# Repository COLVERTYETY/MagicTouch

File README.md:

# Magic touch

This is project implementation of Disney's Touché.

references:

[Dzl's project](http://dzlsevilgeniuslair.blogspot.com/2012/05/arduino-do-touche-dance.html)

[instructables by mashobye](https://www.instructables.com/Touche-for-Arduino-Advanced-touch-sensing/)

[github by illutron](https://github.com/Illutron/AdvancedTouchSensing)

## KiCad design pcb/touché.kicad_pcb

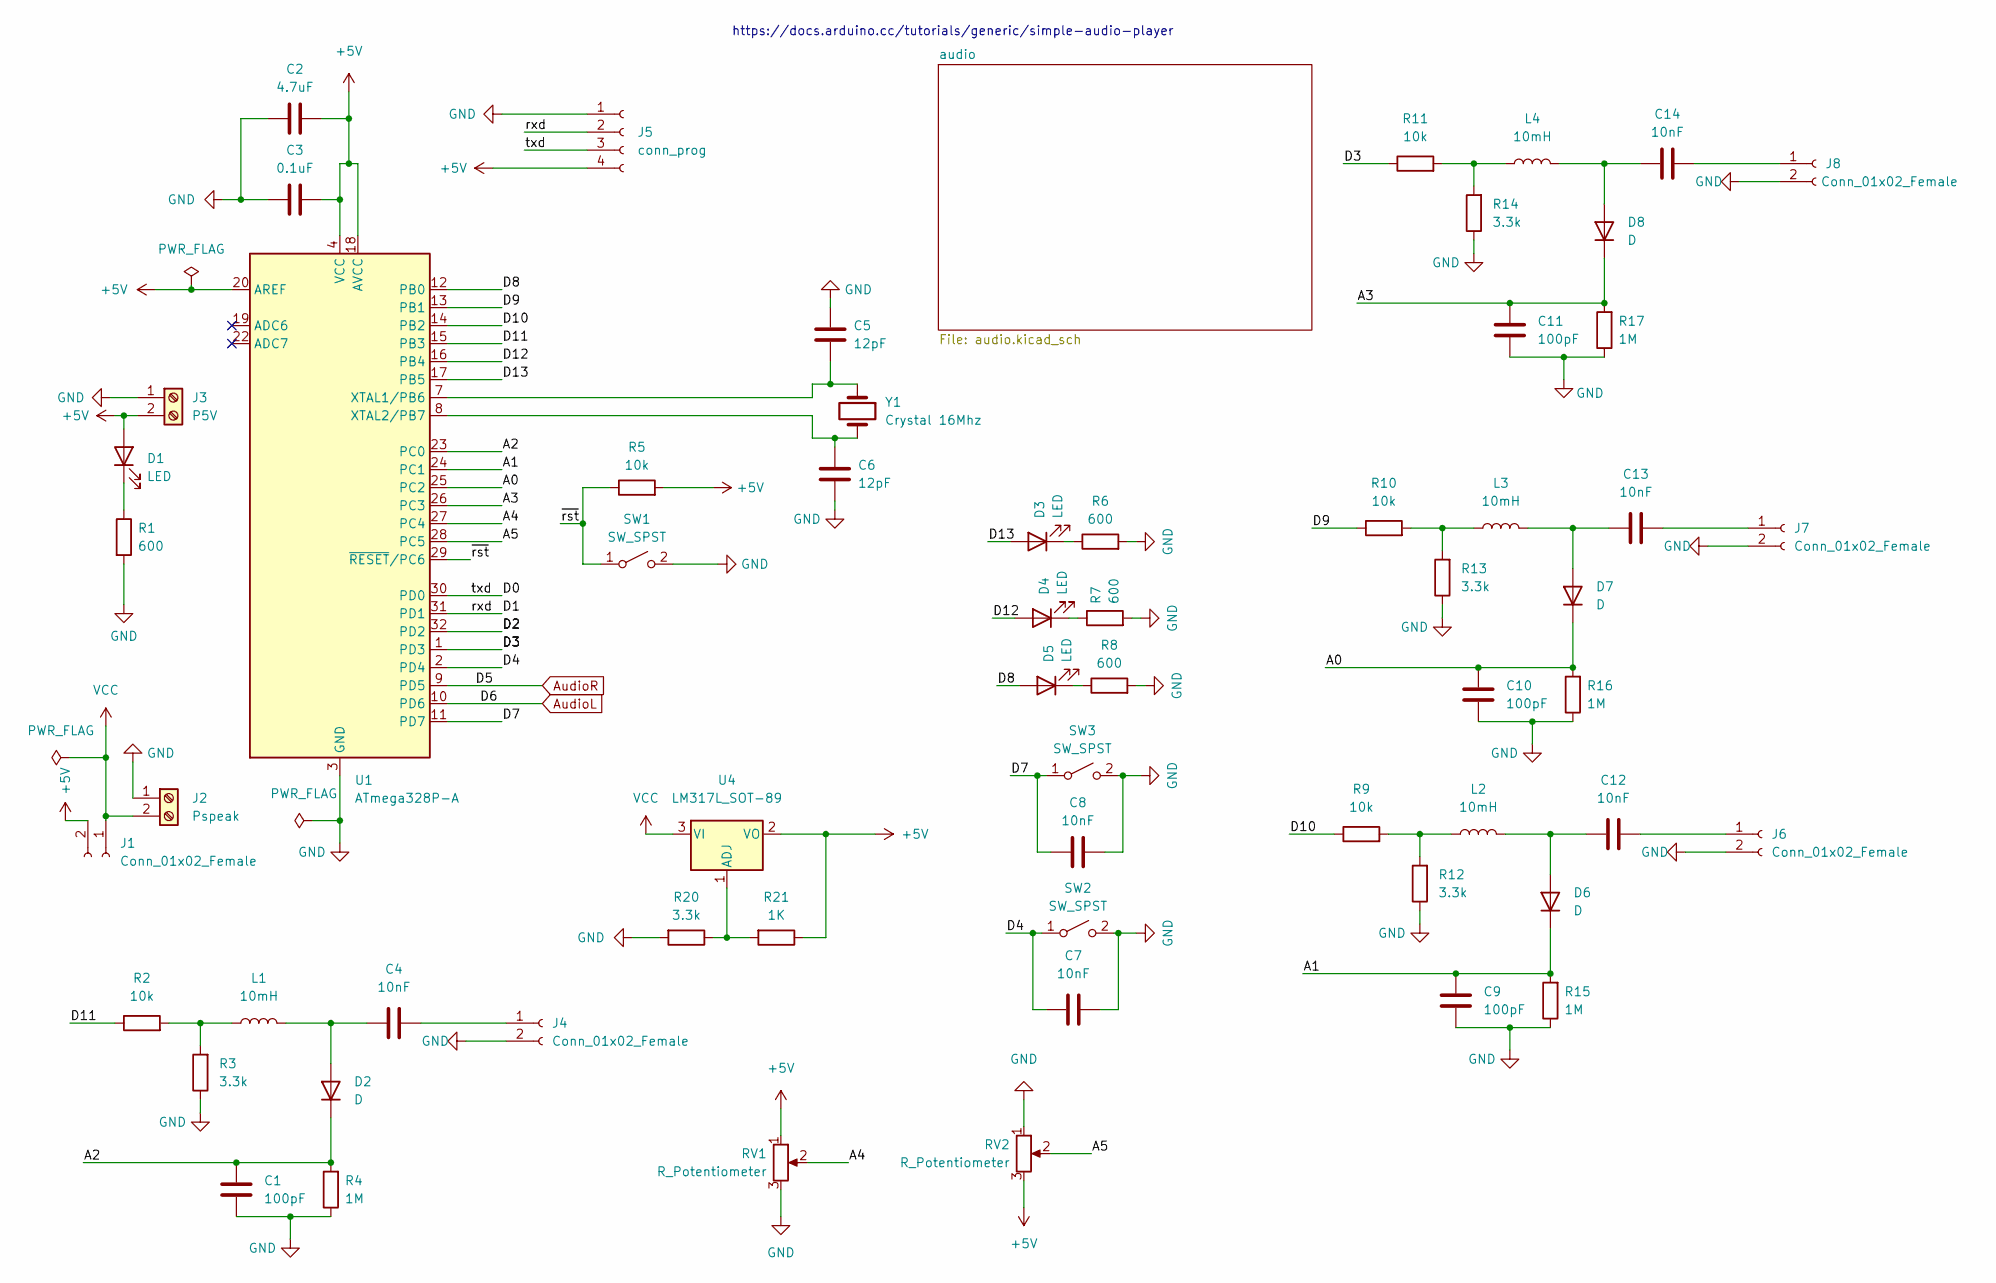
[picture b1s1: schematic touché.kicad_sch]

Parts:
C1, C9, C10, C11: 100pF; C_0603_1608Metric_Pad1.08x0.95mm_HandSolder
C2: 4.7uF; C_0603_1608Metric_Pad1.08x0.95mm_HandSolder
C3: 0.1uF; C_0603_1608Metric_Pad1.08x0.95mm_HandSolder
C4, C7, C8, C12, C13, C14: 10nF; C_0603_1608Metric_Pad1.08x0.95mm_HandSolder
C5, C6: 12pF; C_0603_1608Metric_Pad1.08x0.95mm_HandSolder
D1, D3, D4, D5: LED; LED_0603_1608Metric_Pad1.05x0.95mm_HandSolder
D2, D6, D7, D8: D; D_0603_1608Metric_Pad1.05x0.95mm_HandSolder
J1, J4, J6, J7, J8: Conn_01x02_Female; PinHeader_1x02_P2.54mm_Vertical
J2: Pspeak; TerminalBlock_bornier-2_P5.08mm
J3: P5V; TerminalBlock_bornier-2_P5.08mm
J5: conn_prog; PinHeader_1x04_P2.54mm_Vertical
L1, L2, L3, L4: 10mH; L_Radial_D7.5mm_P5.00mm_Fastron_07P
R1, R6, R7, R8: 600; R_0603_1608Metric_Pad0.98x0.95mm_HandSolder
R2, R5, R9, R10, R11: 10k; R_0603_1608Metric_Pad0.98x0.95mm_HandSolder
R3, R12, R13, R14, R20: 3.3k; R_0603_1608Metric_Pad0.98x0.95mm_HandSolder
R4, R15, R16, R17: 1M; R_0603_1608Metric_Pad0.98x0.95mm_HandSolder
R21: 1K; R_0603_1608Metric_Pad0.98x0.95mm_HandSolder
RV1, RV2: R_Potentiometer; Potentiometer_Bourns_PTV09A-1_Single_Vertical
SW1, SW2, SW3: SW_SPST; SW_Push_1P1T_NO_6x6mm_H9.5mm
U1: ATmega328P-A; TQFP-32_7x7mm_P0.8mm
U4: LM317L_SOT-89; SOT-89-3
Y1: Crystal 16Mhz; ABLS16000MHz20B3HT

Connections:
+5V: C2.1, C3.1, D1.2 (A), J1.2, J3.2, J5.4, R5.2, R21.1, RV1.1, RV2.3, U1.4 (VCC), U1.6 (VCC), U1.18 (AVCC), U1.20 (AREF), U4.2 (VO)
/A0: C10.2, D7.1 (K), R16.2, U1.25 (PC2)
/A1: C9.2, D6.1 (K), R15.2, U1.24 (PC1)
/A2: C1.2, D2.1 (K), R4.2, U1.23 (PC0)
/A3: C11.2, D8.1 (K), R17.2, U1.26 (PC3)
/A4: RV1.2, U1.27 (PC4)
/A5: RV2.2, U1.28 (PC5)
/D0: J5.3, U1.30 (PD0)
/D1: J5.2, U1.31 (PD1)
/D2: U1.32 (PD2)
/D3: R11.1, U1.1 (PD3)
/D4: C7.1, SW2.1 (A), U1.2 (PD4)
/D7: C8.1, SW3.1 (A), U1.11 (PD7)
/D8: D5.2 (A), U1.12 (PB0)
/D9: R10.1, U1.13 (PB1)
/D10: R9.1, U1.14 (PB2)
/D11: R2.1, U1.15 (PB3)
/D12: D4.2 (A), U1.16 (PB4)
/D13: D3.2 (A), U1.17 (PB5)
/~rst: R5.1, SW1.1 (A), U1.29 (~RESET/PC6)
AudioL: U1.10 (PD6); also elsewhere on the board
AudioR: U1.9 (PD5); also elsewhere on the board
GND: C1.1, C2.2, C3.2, C5.1, C6.2, C7.2, C8.2, C9.1, C10.1, C11.1, J2.1, J3.1, J4.2, J5.1, J6.2, J7.2, J8.2, R1.2, R3.1, R4.1, R6.2, R7.2, R8.2, R12.1, R13.1, R14.1, R15.1, R16.1, R17.1, R20.2, RV1.3, RV2.1, SW1.2 (B), SW2.2 (B), SW3.2 (B), U1.3 (GND), U1.5 (GND), U1.21 (GND); also elsewhere on the board
unnamed: C4.1, D2.2 (A), L1.2
unnamed: C4.2, J4.1
unnamed: C5.2, U1.7 (XTAL1/PB6), Y1.1
unnamed: C6.1, U1.8 (XTAL2/PB7), Y1.2
unnamed: C12.1, D6.2 (A), L2.2
unnamed: C12.2, J6.1
unnamed: C13.1, D7.2 (A), L3.2
unnamed: C13.2, J7.1
unnamed: C14.1, D8.2 (A), L4.2
unnamed: C14.2, J8.1
unnamed: D1.1 (K), R1.1
unnamed: D3.1 (K), R6.1
unnamed: D4.1 (K), R7.1
unnamed: D5.1 (K), R8.1
unnamed: L1.1, R2.2, R3.2
unnamed: L2.1, R9.2, R12.2
unnamed: L3.1, R10.2, R13.2
unnamed: L4.1, R11.2, R14.2
unnamed: R20.1, R21.2, U4.1 (ADJ)
VCC: J1.1, J2.2, U4.3 (VI); also elsewhere on the board

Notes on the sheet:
https://docs.arduino.cc/tutorials/generic/simple-audio-player

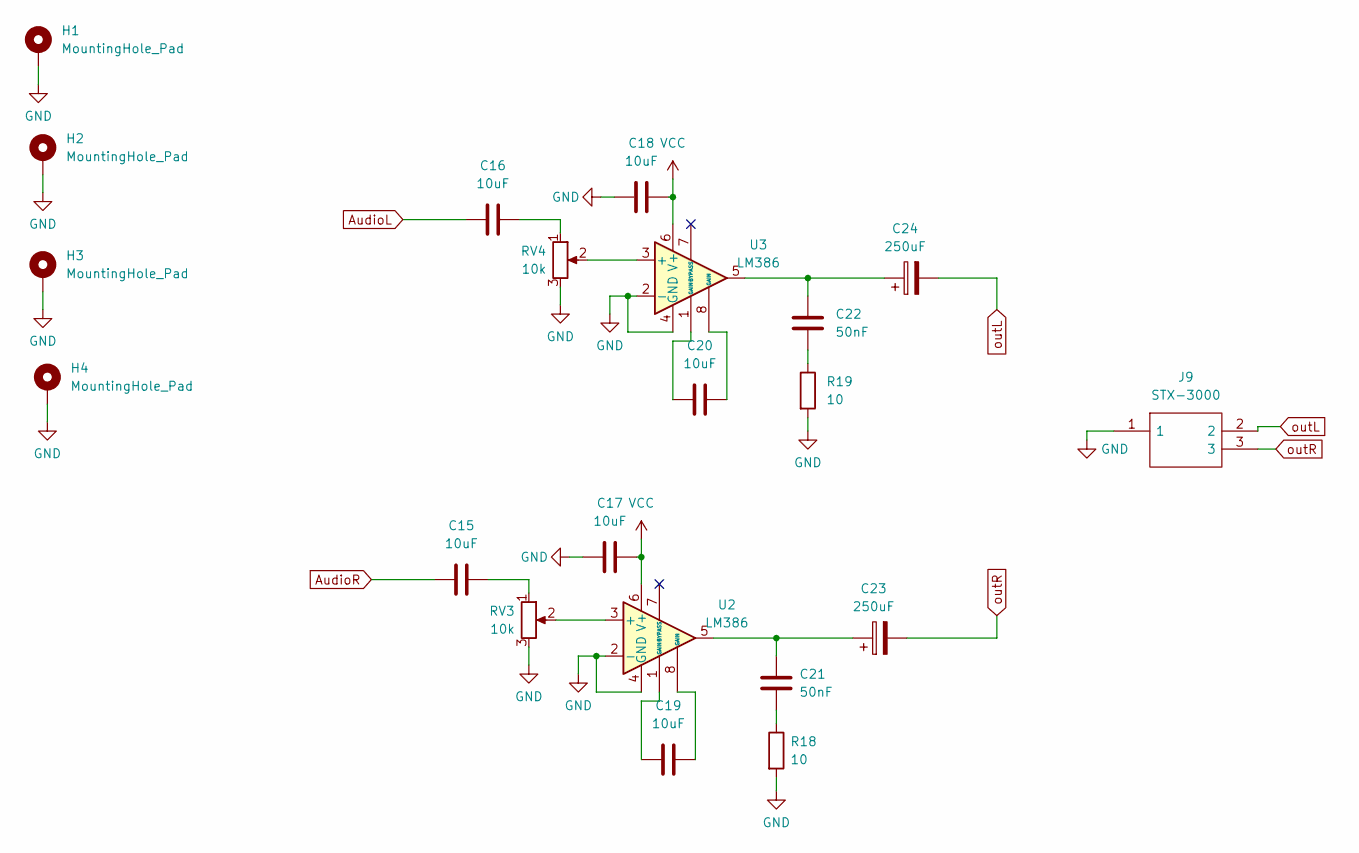
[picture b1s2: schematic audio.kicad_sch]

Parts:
C15, C16, C17, C18, C19, C20: 10uF; C_0603_1608Metric_Pad1.08x0.95mm_HandSolder
C21, C22: 50nF; C_0603_1608Metric_Pad1.08x0.95mm_HandSolder
C23, C24: 250uF; CP_Radial_D6.3mm_P2.50mm
H1, H2, H3, H4: MountingHole_Pad; MountingHole_3.2mm_M3_Pad_Via
J9: STX-3000; STX3000; Mouser Part Number 806-STX-3000
R18, R19: 10; R_0603_1608Metric_Pad0.98x0.95mm_HandSolder
RV3, RV4: 10k; Potentiometer_Bourns_PTV09A-1_Single_Vertical
U2, U3: LM386; DIP-8_W7.62mm

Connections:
AudioL: C16.1; also elsewhere on the board
AudioR: C15.1; also elsewhere on the board
GND: C17.1, C18.1, H1.1, H2.1, H3.1, H4.1, J9.1, R18.2, R19.2, RV3.3, RV4.3, U2.2 (-), U2.4 (GND), U3.2 (-), U3.4 (GND); also elsewhere on the board
unnamed: C15.2, RV3.1
unnamed: C16.2, RV4.1
unnamed: C19.1, U2.8 (GAIN)
unnamed: C19.2, U2.1 (GAIN)
unnamed: C20.1, U3.8 (GAIN)
unnamed: C20.2, U3.1 (GAIN)
unnamed: C21.1, R18.1
unnamed: C21.2, C23.1, U2.5
unnamed: C22.1, R19.1
unnamed: C22.2, C24.1, U3.5
unnamed: RV3.2, U2.3 (+)
unnamed: RV4.2, U3.3 (+)
VCC: C17.2, C18.2, U2.6 (V+), U3.6 (V+); also elsewhere on the board
outL: C24.2, J9.2
outR: C23.2, J9.3

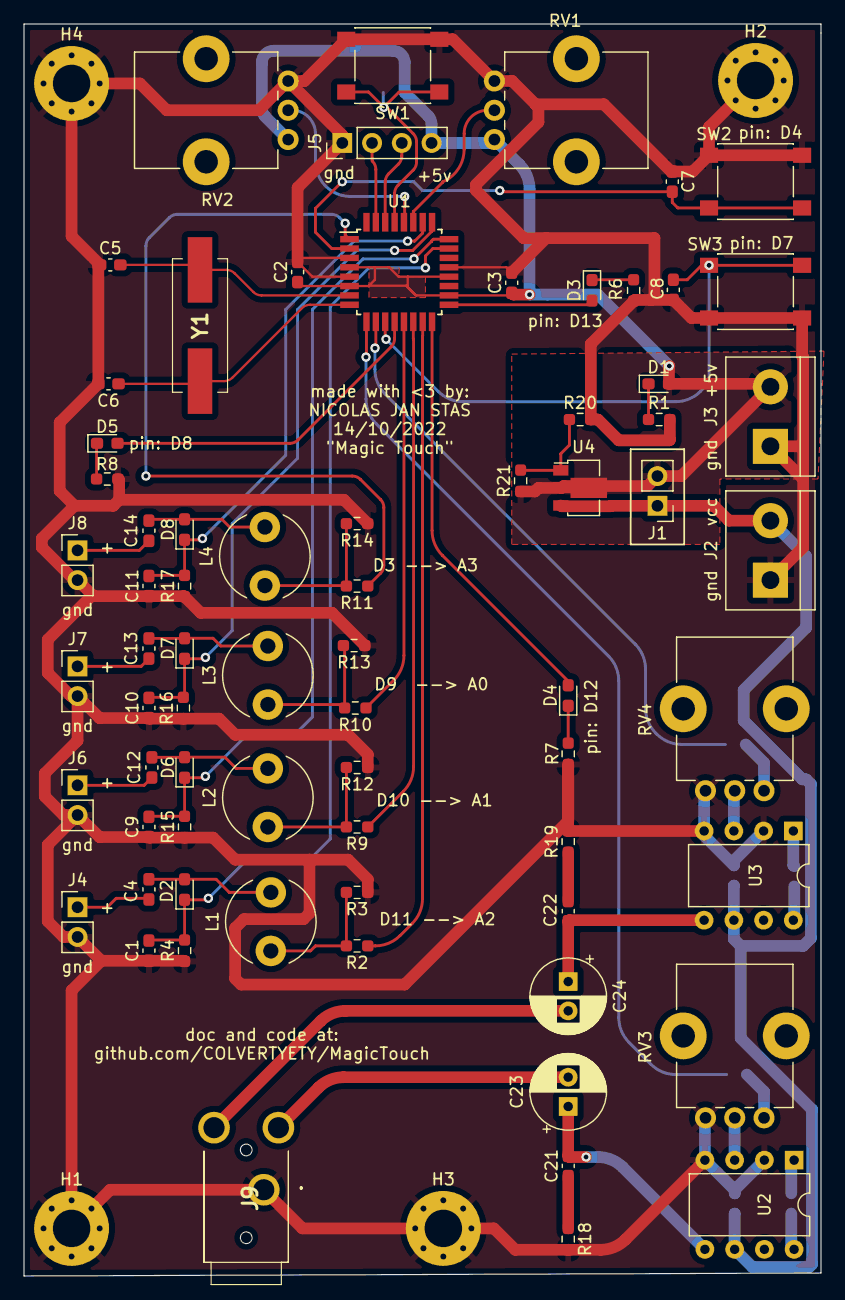
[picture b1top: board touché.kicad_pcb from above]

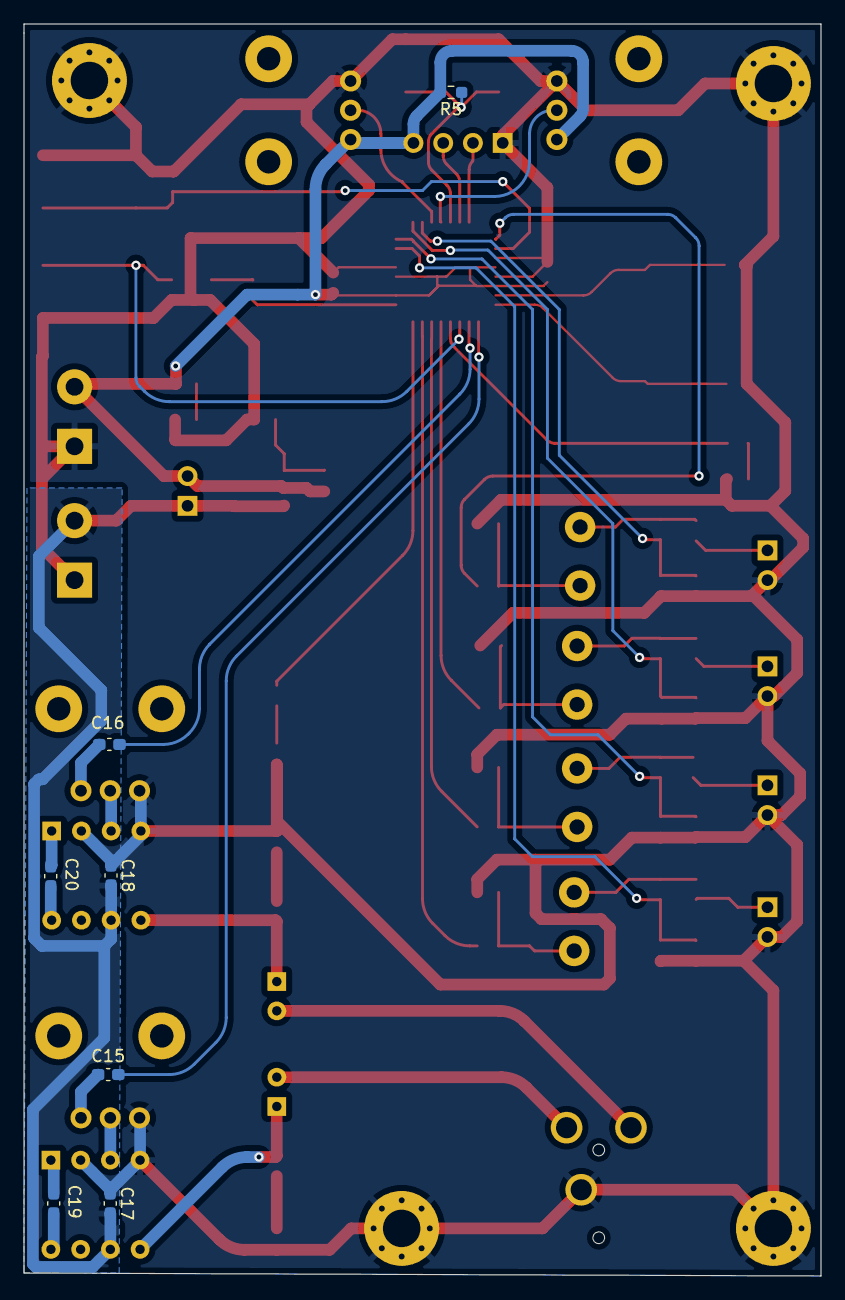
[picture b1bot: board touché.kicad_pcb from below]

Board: 2 copper layers, 68.1 x 106.9 mm, 82 parts (7 on the bottom side), 56 nets.

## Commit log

2022-11-15 fixed typos
